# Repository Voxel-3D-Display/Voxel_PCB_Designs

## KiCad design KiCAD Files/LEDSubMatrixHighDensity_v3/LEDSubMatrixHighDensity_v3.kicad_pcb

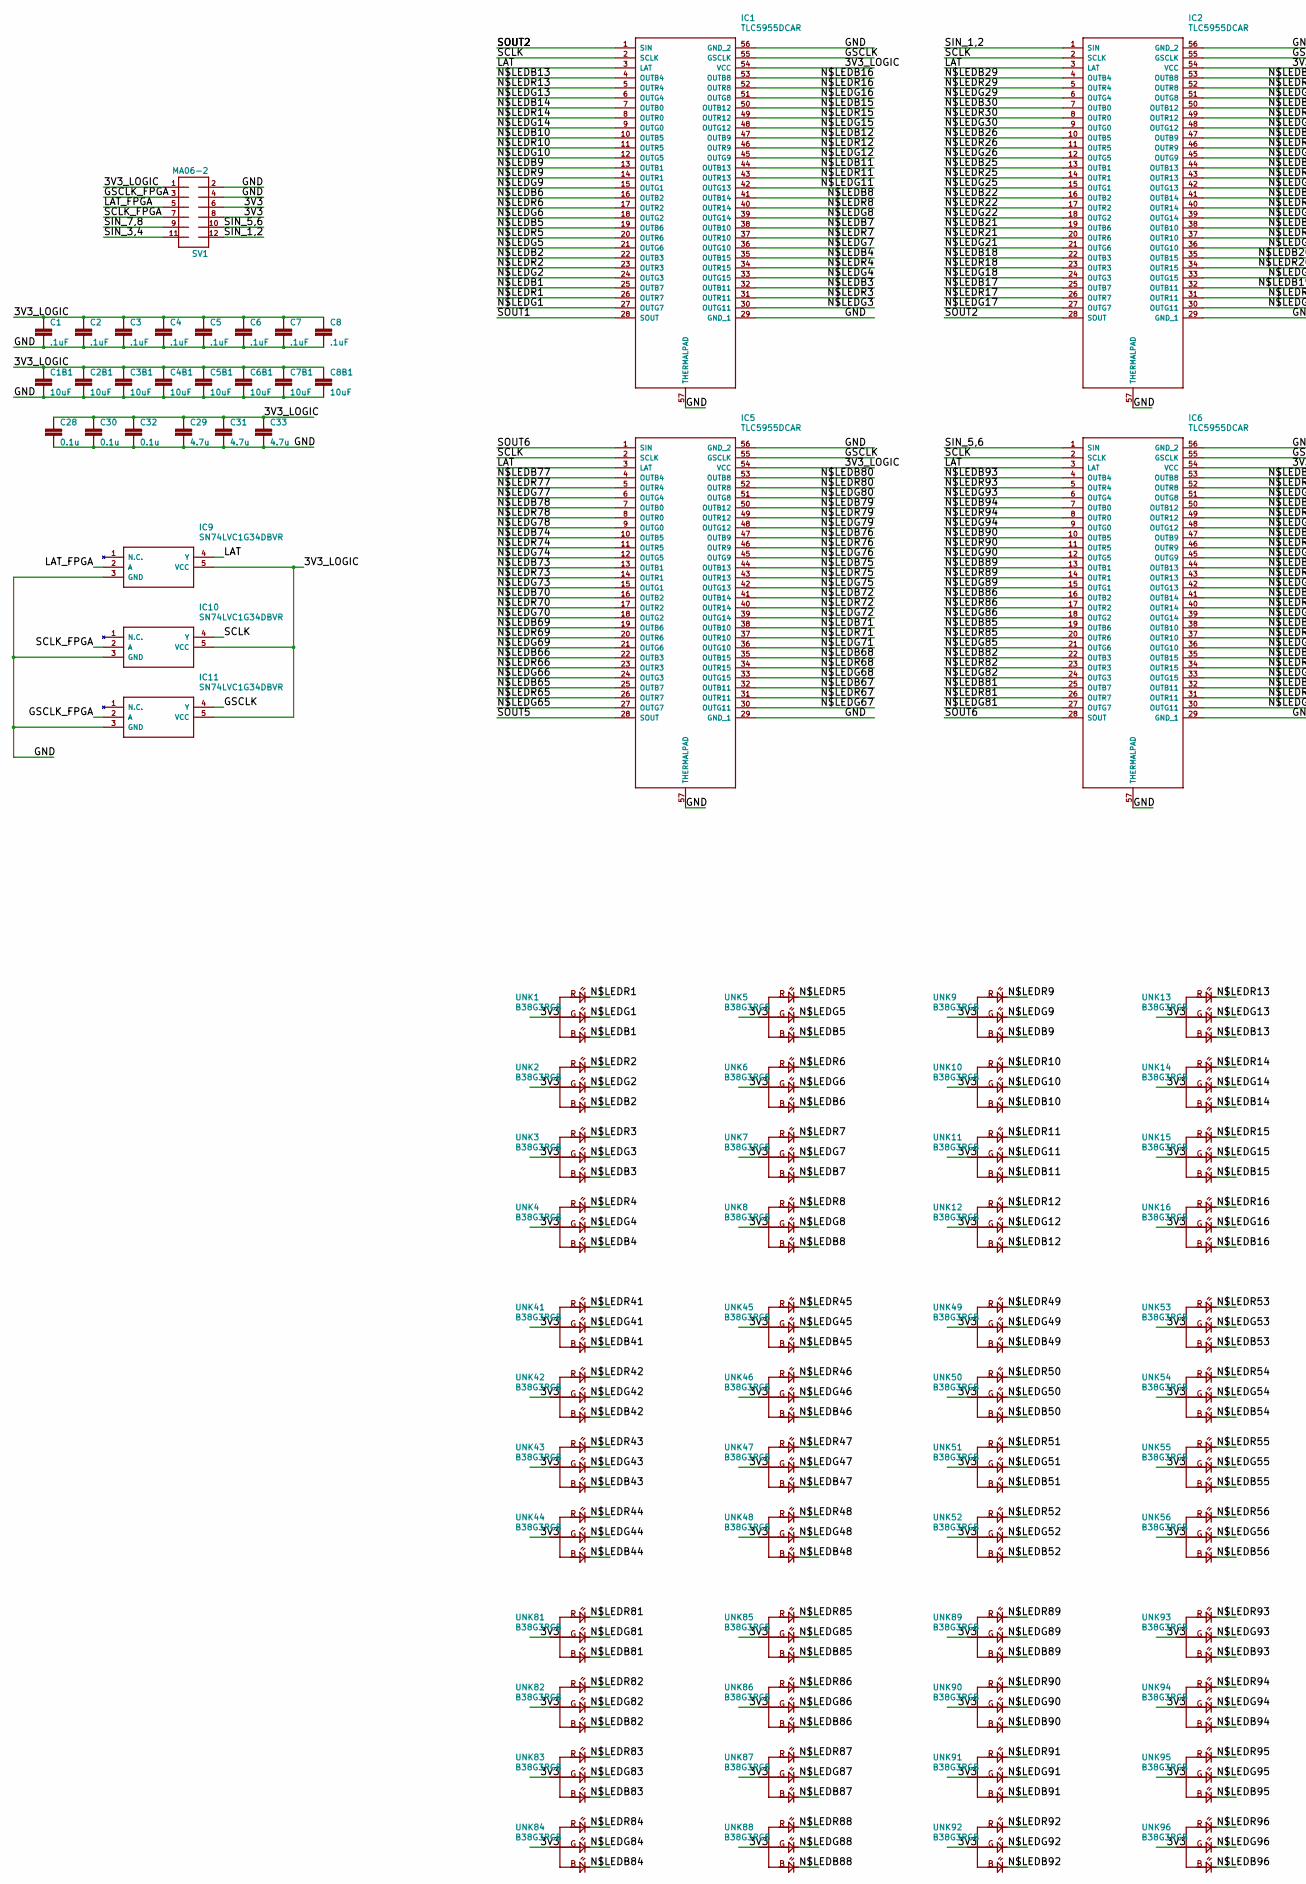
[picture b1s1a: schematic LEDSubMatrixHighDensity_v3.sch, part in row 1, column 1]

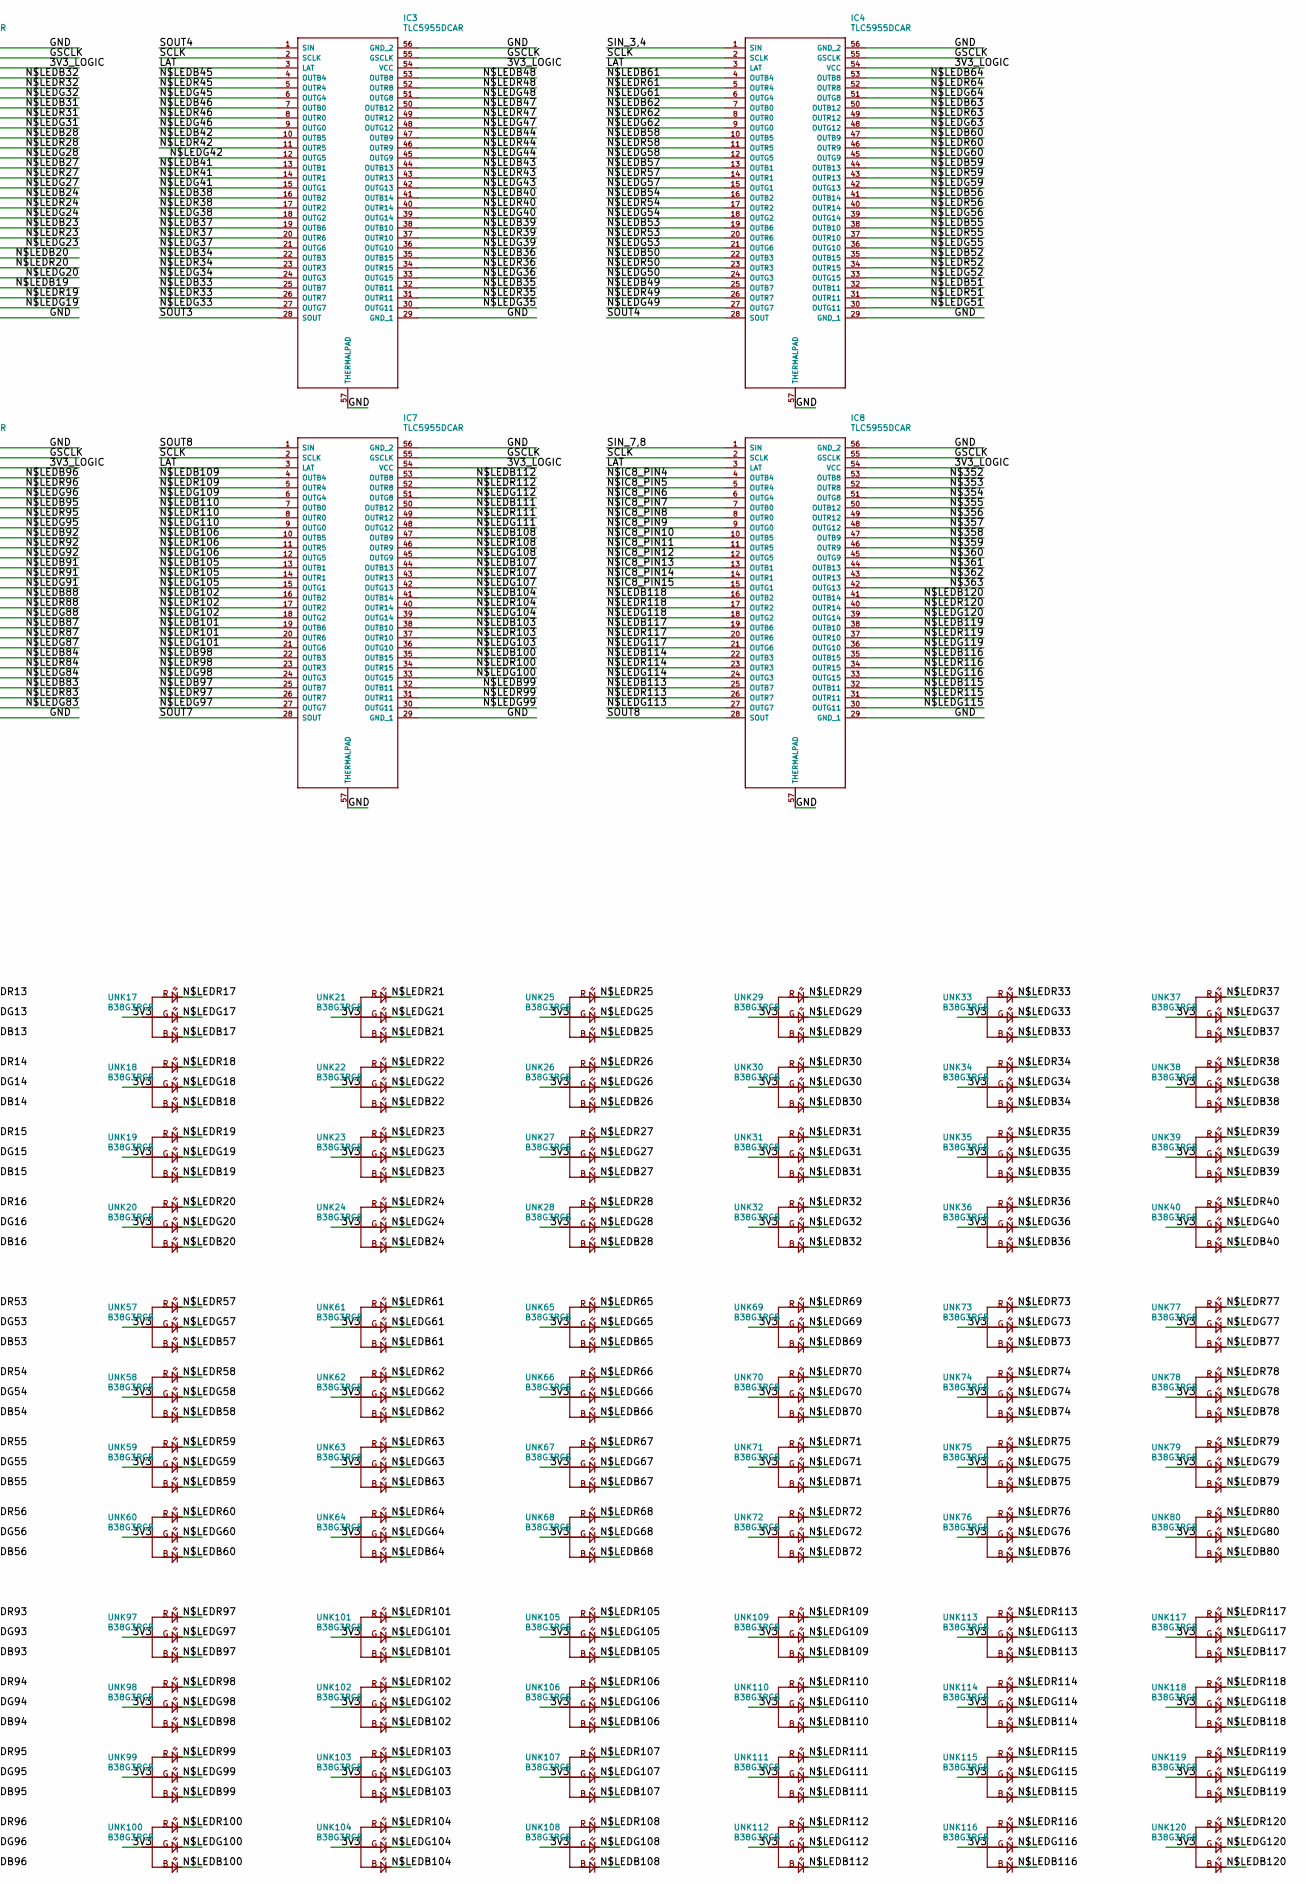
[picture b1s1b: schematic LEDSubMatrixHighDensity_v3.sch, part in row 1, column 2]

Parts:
C1, C2, C3, C4, C5, C6, C7, C8: .1uF; C0402
C1B1, C2B1, C3B1, C4B1, C5B1, C6B1, C7B1, C8B1: 10uF; C0402
C28, C30, C32: 0.1u; C0402
C29, C31, C33: 4.7u; C0402
IC1, IC2, IC3, IC4, IC5, IC6, IC7, IC8: TLC5955DCAR; SOP50P810X120-57N
IC9, IC10, IC11: SN74LVC1G34DBVR; SOT95P280X145-5N
SV1: MA06-2
UNK1, UNK2, UNK3, UNK4, UNK5, UNK6, UNK7, UNK8, UNK9, UNK10, UNK11, UNK12, UNK13, UNK14, UNK15, UNK16, UNK17, UNK18, UNK19, UNK20, UNK21, UNK22, UNK23, UNK24, UNK25, UNK26, UNK27, UNK28, UNK29, UNK30, UNK31, UNK32, UNK33, UNK34, UNK35, UNK36, UNK37, UNK38, UNK39, UNK40, UNK41, UNK42, UNK43, UNK44, UNK45, UNK46, UNK47, UNK48, UNK49, UNK50, UNK51, UNK52, UNK53, UNK54, UNK55, UNK56, UNK57, UNK58, UNK59, UNK60, UNK61, UNK62, UNK63, UNK64, UNK65, UNK66, UNK67, UNK68, UNK69, UNK70, UNK71, UNK72, UNK73, UNK74, UNK75, UNK76, UNK77, UNK78, UNK79, UNK80, UNK81, UNK82, UNK83, UNK84, UNK85, UNK86, UNK87, UNK88, UNK89, UNK90, UNK91, UNK92, UNK93, UNK94, UNK95, UNK96, UNK97, UNK98, UNK99, UNK100, UNK101, UNK102, UNK103, UNK104, UNK105, UNK106, UNK107, UNK108, UNK109, UNK110, UNK111, UNK112, UNK113, UNK114, UNK115, UNK116, UNK117, UNK118, UNK119, UNK120: B38G3RGB

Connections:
/3V3: SV1.6, SV1.8, UNK1.3 (COM), UNK2.3 (COM), UNK3.3 (COM), UNK4.3 (COM), UNK5.3 (COM), UNK6.3 (COM), UNK7.3 (COM), UNK8.3 (COM), UNK9.3 (COM), UNK10.3 (COM), UNK11.3 (COM), UNK12.3 (COM), UNK13.3 (COM), UNK14.3 (COM), UNK15.3 (COM), UNK16.3 (COM), UNK17.3 (COM), UNK18.3 (COM), UNK19.3 (COM), UNK20.3 (COM), UNK21.3 (COM), UNK22.3 (COM), UNK23.3 (COM), UNK24.3 (COM), UNK25.3 (COM), UNK26.3 (COM), UNK27.3 (COM), UNK28.3 (COM), UNK29.3 (COM), UNK30.3 (COM), UNK31.3 (COM), UNK32.3 (COM), UNK33.3 (COM), UNK34.3 (COM), UNK35.3 (COM), UNK36.3 (COM), UNK37.3 (COM), UNK38.3 (COM), UNK39.3 (COM), UNK40.3 (COM), UNK41.3 (COM), UNK42.3 (COM), UNK43.3 (COM), UNK44.3 (COM), UNK45.3 (COM), UNK46.3 (COM), UNK47.3 (COM), UNK48.3 (COM), UNK49.3 (COM), UNK50.3 (COM), UNK51.3 (COM), UNK52.3 (COM), UNK53.3 (COM), UNK54.3 (COM), UNK55.3 (COM), UNK56.3 (COM), UNK57.3 (COM), UNK58.3 (COM), UNK59.3 (COM), UNK60.3 (COM), UNK61.3 (COM), UNK62.3 (COM), UNK63.3 (COM), UNK64.3 (COM), UNK65.3 (COM), UNK66.3 (COM), UNK67.3 (COM), UNK68.3 (COM), UNK69.3 (COM), UNK70.3 (COM), UNK71.3 (COM), UNK72.3 (COM), UNK73.3 (COM), UNK74.3 (COM), UNK75.3 (COM), UNK76.3 (COM), UNK77.3 (COM), UNK78.3 (COM), UNK79.3 (COM), UNK80.3 (COM), UNK81.3 (COM), UNK82.3 (COM), UNK83.3 (COM), UNK84.3 (COM), UNK85.3 (COM), UNK86.3 (COM), UNK87.3 (COM), UNK88.3 (COM), UNK89.3 (COM), UNK90.3 (COM), UNK91.3 (COM), UNK92.3 (COM), UNK93.3 (COM), UNK94.3 (COM), UNK95.3 (COM), UNK96.3 (COM), UNK97.3 (COM), UNK98.3 (COM), UNK99.3 (COM), UNK100.3 (COM), UNK101.3 (COM), UNK102.3 (COM), UNK103.3 (COM), UNK104.3 (COM), UNK105.3 (COM), UNK106.3 (COM), UNK107.3 (COM), UNK108.3 (COM), UNK109.3 (COM), UNK110.3 (COM), UNK111.3 (COM), UNK112.3 (COM), UNK113.3 (COM), UNK114.3 (COM), UNK115.3 (COM), UNK116.3 (COM), UNK117.3 (COM), UNK118.3 (COM), UNK119.3 (COM), UNK120.3 (COM)
/3V3_LOGIC: C1.1, C1B1.1, C2.1, C2B1.1, C3.1, C3B1.1, C4.1, C4B1.1, C5.1, C5B1.1, C6.1, C6B1.1, C7.1, C7B1.1, C8.1, C8B1.1, C28.1, C29.1, C30.1, C31.1, C32.1, C33.1, IC1.54 (VCC), IC2.54 (VCC), IC3.54 (VCC), IC4.54 (VCC), IC5.54 (VCC), IC6.54 (VCC), IC7.54 (VCC), IC8.54 (VCC), IC9.5 (VCC), IC10.5 (VCC), IC11.5 (VCC), SV1.1
/GND: C1.2, C1B1.2, C2.2, C2B1.2, C3.2, C3B1.2, C4.2, C4B1.2, C5.2, C5B1.2, C6.2, C6B1.2, C7.2, C7B1.2, C8.2, C8B1.2, C28.2, C29.2, C30.2, C31.2, C32.2, C33.2, IC1.56 (GND_2), IC2.56 (GND_2), IC3.56 (GND_2), IC4.56 (GND_2), IC5.29 (GND_1), IC5.56 (GND_2), IC5.57 (THERMALPAD), IC6.29 (GND_1), IC6.56 (GND_2), IC6.57 (THERMALPAD), IC7.29 (GND_1), IC7.56 (GND_2), IC7.57 (THERMALPAD), IC8.29 (GND_1), IC8.56 (GND_2), IC8.57 (THERMALPAD), IC9.3 (GND), IC10.3 (GND), IC11.3 (GND), SV1.2, SV1.4
/GSCLK: IC1.55 (GSCLK), IC2.55 (GSCLK), IC3.55 (GSCLK), IC4.55 (GSCLK), IC5.55 (GSCLK), IC6.55 (GSCLK), IC7.55 (GSCLK), IC8.55 (GSCLK), IC11.4 (Y)
/GSCLK_FPGA: IC11.2 (A), SV1.3
/LAT: IC1.3 (LAT), IC2.3 (LAT), IC3.3 (LAT), IC4.3 (LAT), IC5.3 (LAT), IC6.3 (LAT), IC7.3 (LAT), IC8.3 (LAT), IC9.4 (Y)
/LAT_FPGA: IC9.2 (A), SV1.5
/N$352: IC8.53 (OUTB8)
/N$353: IC8.52 (OUTR8)
/N$354: IC8.51 (OUTG8)
/N$355: IC8.50 (OUTB12)
/N$356: IC8.49 (OUTR12)
/N$357: IC8.48 (OUTG12)
/N$358: IC8.47 (OUTB9)
/N$359: IC8.46 (OUTR9)
/N$360: IC8.45 (OUTG9)
/N$361: IC8.44 (OUTB13)
/N$362: IC8.43 (OUTR13)
/N$363: IC8.42 (OUTG13)
/N$IC8_PIN4: IC8.4 (OUTB4)
/N$IC8_PIN5: IC8.5 (OUTR4)
/N$IC8_PIN6: IC8.6 (OUTG4)
/N$IC8_PIN7: IC8.7 (OUTB0)
/N$IC8_PIN8: IC8.8 (OUTR0)
/N$IC8_PIN9: IC8.9 (OUTG0)
/N$IC8_PIN10: IC8.10 (OUTB5)
/N$IC8_PIN11: IC8.11 (OUTR5)
/N$IC8_PIN12: IC8.12 (OUTG5)
/N$IC8_PIN13: IC8.13 (OUTB1)
/N$IC8_PIN14: IC8.14 (OUTR1)
/N$IC8_PIN15: IC8.15 (OUTG1)
/N$LEDB1: UNK1.2 (BLUE)
/N$LEDB2: IC1.22 (OUTB3), UNK2.2 (BLUE)
/N$LEDB3: UNK3.2 (BLUE)
/N$LEDB4: IC1.35 (OUTB15), UNK4.2 (BLUE)
/N$LEDB5: IC1.19 (OUTB6), UNK5.2 (BLUE)
/N$LEDB6: IC1.16 (OUTB2), UNK6.2 (BLUE)
/N$LEDB7: IC1.38 (OUTB10), UNK7.2 (BLUE)
/N$LEDB8: IC1.41 (OUTB14), UNK8.2 (BLUE)
/N$LEDB9: IC1.13 (OUTB1), UNK9.2 (BLUE)
/N$LEDB10: IC1.10 (OUTB5), UNK10.2 (BLUE)
/N$LEDB11: IC1.44 (OUTB13), UNK11.2 (BLUE)
/N$LEDB12: IC1.47 (OUTB9), UNK12.2 (BLUE)
/N$LEDB13: IC1.4 (OUTB4), UNK13.2 (BLUE)
/N$LEDB14: IC1.7 (OUTB0), UNK14.2 (BLUE)
/N$LEDB15: IC1.50 (OUTB12), UNK15.2 (BLUE)
/N$LEDB16: IC1.53 (OUTB8), UNK16.2 (BLUE)
/N$LEDB17: UNK17.2 (BLUE)
/N$LEDB18: IC2.22 (OUTB3), UNK18.2 (BLUE)
/N$LEDB19: UNK19.2 (BLUE)
/N$LEDB20: IC2.35 (OUTB15), UNK20.2 (BLUE)
/N$LEDB21: IC2.19 (OUTB6), UNK21.2 (BLUE)
/N$LEDB22: IC2.16 (OUTB2), UNK22.2 (BLUE)
/N$LEDB23: IC2.38 (OUTB10), UNK23.2 (BLUE)
/N$LEDB24: IC2.41 (OUTB14), UNK24.2 (BLUE)
/N$LEDB25: IC2.13 (OUTB1), UNK25.2 (BLUE)
/N$LEDB26: IC2.10 (OUTB5), UNK26.2 (BLUE)
/N$LEDB27: IC2.44 (OUTB13), UNK27.2 (BLUE)
/N$LEDB28: IC2.47 (OUTB9), UNK28.2 (BLUE)
/N$LEDB29: IC2.4 (OUTB4), UNK29.2 (BLUE)
/N$LEDB30: IC2.7 (OUTB0), UNK30.2 (BLUE)
/N$LEDB31: IC2.50 (OUTB12), UNK31.2 (BLUE)
/N$LEDB32: IC2.53 (OUTB8), UNK32.2 (BLUE)
/N$LEDB33: UNK33.2 (BLUE)
/N$LEDB34: IC3.22 (OUTB3), UNK34.2 (BLUE)
/N$LEDB35: UNK35.2 (BLUE)
/N$LEDB36: IC3.35 (OUTB15), UNK36.2 (BLUE)
/N$LEDB37: IC3.19 (OUTB6), UNK37.2 (BLUE)
/N$LEDB38: IC3.16 (OUTB2), UNK38.2 (BLUE)
/N$LEDB39: IC3.38 (OUTB10), UNK39.2 (BLUE)
/N$LEDB40: IC3.41 (OUTB14), UNK40.2 (BLUE)
/N$LEDB41: IC3.13 (OUTB1), UNK41.2 (BLUE)
/N$LEDB42: IC3.10 (OUTB5), UNK42.2 (BLUE)
/N$LEDB43: IC3.44 (OUTB13), UNK43.2 (BLUE)
/N$LEDB44: IC3.47 (OUTB9), UNK44.2 (BLUE)
/N$LEDB45: IC3.4 (OUTB4), UNK45.2 (BLUE)
/N$LEDB46: IC3.7 (OUTB0), UNK46.2 (BLUE)
/N$LEDB47: IC3.50 (OUTB12), UNK47.2 (BLUE)
/N$LEDB48: IC3.53 (OUTB8), UNK48.2 (BLUE)
/N$LEDB49: UNK49.2 (BLUE)
/N$LEDB50: IC4.22 (OUTB3), UNK50.2 (BLUE)
/N$LEDB51: UNK51.2 (BLUE)
/N$LEDB52: IC4.35 (OUTB15), UNK52.2 (BLUE)
/N$LEDB53: IC4.19 (OUTB6), UNK53.2 (BLUE)
/N$LEDB54: IC4.16 (OUTB2), UNK54.2 (BLUE)
/N$LEDB55: IC4.38 (OUTB10), UNK55.2 (BLUE)
/N$LEDB56: IC4.41 (OUTB14), UNK56.2 (BLUE)
/N$LEDB57: IC4.13 (OUTB1), UNK57.2 (BLUE)
/N$LEDB58: IC4.10 (OUTB5), UNK58.2 (BLUE)
/N$LEDB59: IC4.44 (OUTB13), UNK59.2 (BLUE)
/N$LEDB60: IC4.47 (OUTB9), UNK60.2 (BLUE)
/N$LEDB61: IC4.4 (OUTB4), UNK61.2 (BLUE)
/N$LEDB62: IC4.7 (OUTB0), UNK62.2 (BLUE)
/N$LEDB63: IC4.50 (OUTB12), UNK63.2 (BLUE)
/N$LEDB64: IC4.53 (OUTB8), UNK64.2 (BLUE)
/N$LEDB65: IC5.25 (OUTB7), UNK65.2 (BLUE)
/N$LEDB66: IC5.22 (OUTB3), UNK66.2 (BLUE)
/N$LEDB67: IC5.32 (OUTB11), UNK67.2 (BLUE)
/N$LEDB68: IC5.35 (OUTB15), UNK68.2 (BLUE)
/N$LEDB69: IC5.19 (OUTB6), UNK69.2 (BLUE)
/N$LEDB70: IC5.16 (OUTB2), UNK70.2 (BLUE)
/N$LEDB71: IC5.38 (OUTB10), UNK71.2 (BLUE)
/N$LEDB72: IC5.41 (OUTB14), UNK72.2 (BLUE)
/N$LEDB73: IC5.13 (OUTB1), UNK73.2 (BLUE)
/N$LEDB74: IC5.10 (OUTB5), UNK74.2 (BLUE)
/N$LEDB75: IC5.44 (OUTB13), UNK75.2 (BLUE)
/N$LEDB76: IC5.47 (OUTB9), UNK76.2 (BLUE)
/N$LEDB77: IC5.4 (OUTB4), UNK77.2 (BLUE)
/N$LEDB78: IC5.7 (OUTB0), UNK78.2 (BLUE)
/N$LEDB79: IC5.50 (OUTB12), UNK79.2 (BLUE)
/N$LEDB80: IC5.53 (OUTB8), UNK80.2 (BLUE)
/N$LEDB81: IC6.25 (OUTB7), UNK81.2 (BLUE)
/N$LEDB82: IC6.22 (OUTB3), UNK82.2 (BLUE)
/N$LEDB83: IC6.32 (OUTB11), UNK83.2 (BLUE)
/N$LEDB84: IC6.35 (OUTB15), UNK84.2 (BLUE)
/N$LEDB85: IC6.19 (OUTB6), UNK85.2 (BLUE)
/N$LEDB86: IC6.16 (OUTB2), UNK86.2 (BLUE)
/N$LEDB87: IC6.38 (OUTB10), UNK87.2 (BLUE)
/N$LEDB88: IC6.41 (OUTB14), UNK88.2 (BLUE)
/N$LEDB89: IC6.13 (OUTB1), UNK89.2 (BLUE)
/N$LEDB90: IC6.10 (OUTB5), UNK90.2 (BLUE)
/N$LEDB91: IC6.44 (OUTB13), UNK91.2 (BLUE)
/N$LEDB92: IC6.47 (OUTB9), UNK92.2 (BLUE)
/N$LEDB93: IC6.4 (OUTB4), UNK93.2 (BLUE)
/N$LEDB94: IC6.7 (OUTB0), UNK94.2 (BLUE)
/N$LEDB95: IC6.50 (OUTB12), UNK95.2 (BLUE)
/N$LEDB96: IC6.53 (OUTB8), UNK96.2 (BLUE)
/N$LEDB97: IC7.25 (OUTB7), UNK97.2 (BLUE)
/N$LEDB98: IC7.22 (OUTB3), UNK98.2 (BLUE)
/N$LEDB99: IC7.32 (OUTB11), UNK99.2 (BLUE)
/N$LEDB100: IC7.35 (OUTB15), UNK100.2 (BLUE)
/N$LEDB101: IC7.19 (OUTB6), UNK101.2 (BLUE)
/N$LEDB102: IC7.16 (OUTB2), UNK102.2 (BLUE)
/N$LEDB103: IC7.38 (OUTB10), UNK103.2 (BLUE)
/N$LEDB104: IC7.41 (OUTB14), UNK104.2 (BLUE)
/N$LEDB105: IC7.13 (OUTB1), UNK105.2 (BLUE)
/N$LEDB106: IC7.10 (OUTB5), UNK106.2 (BLUE)
/N$LEDB107: IC7.44 (OUTB13), UNK107.2 (BLUE)
/N$LEDB108: IC7.47 (OUTB9), UNK108.2 (BLUE)
/N$LEDB109: IC7.4 (OUTB4), UNK109.2 (BLUE)
/N$LEDB110: IC7.7 (OUTB0), UNK110.2 (BLUE)
/N$LEDB111: IC7.50 (OUTB12), UNK111.2 (BLUE)
/N$LEDB112: IC7.53 (OUTB8), UNK112.2 (BLUE)
/N$LEDB113: IC8.25 (OUTB7), UNK113.2 (BLUE)
/N$LEDB114: IC8.22 (OUTB3), UNK114.2 (BLUE)
/N$LEDB115: IC8.32 (OUTB11), UNK115.2 (BLUE)
/N$LEDB116: IC8.35 (OUTB15), UNK116.2 (BLUE)
/N$LEDB117: IC8.19 (OUTB6), UNK117.2 (BLUE)
/N$LEDB118: IC8.16 (OUTB2), UNK118.2 (BLUE)
/N$LEDB119: IC8.38 (OUTB10), UNK119.2 (BLUE)
/N$LEDB120: IC8.41 (OUTB14), UNK120.2 (BLUE)
/N$LEDG1: UNK1.1 (GREEN)
/N$LEDG2: UNK2.1 (GREEN)
/N$LEDG3: UNK3.1 (GREEN)
/N$LEDG4: UNK4.1 (GREEN)
/N$LEDG5: IC1.21 (OUTG6), UNK5.1 (GREEN)
/N$LEDG6: IC1.18 (OUTG2), UNK6.1 (GREEN)
/N$LEDG7: IC1.36 (OUTG10), UNK7.1 (GREEN)
/N$LEDG8: IC1.39 (OUTG14), UNK8.1 (GREEN)
/N$LEDG9: IC1.15 (OUTG1), UNK9.1 (GREEN)
/N$LEDG10: IC1.12 (OUTG5), UNK10.1 (GREEN)
/N$LEDG11: IC1.42 (OUTG13), UNK11.1 (GREEN)
/N$LEDG12: IC1.45 (OUTG9), UNK12.1 (GREEN)
/N$LEDG13: IC1.6 (OUTG4), UNK13.1 (GREEN)
/N$LEDG14: IC1.9 (OUTG0), UNK14.1 (GREEN)
/N$LEDG15: IC1.48 (OUTG12), UNK15.1 (GREEN)
/N$LEDG16: IC1.51 (OUTG8), UNK16.1 (GREEN)
/N$LEDG17: UNK17.1 (GREEN)
/N$LEDG18: UNK18.1 (GREEN)
/N$LEDG19: UNK19.1 (GREEN)
/N$LEDG20: UNK20.1 (GREEN)
/N$LEDG21: IC2.21 (OUTG6), UNK21.1 (GREEN)
/N$LEDG22: IC2.18 (OUTG2), UNK22.1 (GREEN)
/N$LEDG23: IC2.36 (OUTG10), UNK23.1 (GREEN)
/N$LEDG24: IC2.39 (OUTG14), UNK24.1 (GREEN)
/N$LEDG25: IC2.15 (OUTG1), UNK25.1 (GREEN)
/N$LEDG26: IC2.12 (OUTG5), UNK26.1 (GREEN)
/N$LEDG27: IC2.42 (OUTG13), UNK27.1 (GREEN)
/N$LEDG28: IC2.45 (OUTG9), UNK28.1 (GREEN)
/N$LEDG29: IC2.6 (OUTG4), UNK29.1 (GREEN)
/N$LEDG30: IC2.9 (OUTG0), UNK30.1 (GREEN)
/N$LEDG31: IC2.48 (OUTG12), UNK31.1 (GREEN)
/N$LEDG32: IC2.51 (OUTG8), UNK32.1 (GREEN)
/N$LEDG33: UNK33.1 (GREEN)
/N$LEDG34: UNK34.1 (GREEN)
/N$LEDG35: UNK35.1 (GREEN)
/N$LEDG36: UNK36.1 (GREEN)
/N$LEDG37: IC3.21 (OUTG6), UNK37.1 (GREEN)
/N$LEDG38: IC3.18 (OUTG2), UNK38.1 (GREEN)
/N$LEDG39: IC3.36 (OUTG10), UNK39.1 (GREEN)
/N$LEDG40: IC3.39 (OUTG14), UNK40.1 (GREEN)
/N$LEDG41: IC3.15 (OUTG1), UNK41.1 (GREEN)
/N$LEDG42: IC3.12 (OUTG5), UNK42.1 (GREEN)
/N$LEDG43: IC3.42 (OUTG13), UNK43.1 (GREEN)
/N$LEDG44: IC3.45 (OUTG9), UNK44.1 (GREEN)
/N$LEDG45: IC3.6 (OUTG4), UNK45.1 (GREEN)
/N$LEDG46: IC3.9 (OUTG0), UNK46.1 (GREEN)
/N$LEDG47: IC3.48 (OUTG12), UNK47.1 (GREEN)
/N$LEDG48: IC3.51 (OUTG8), UNK48.1 (GREEN)
/N$LEDG49: UNK49.1 (GREEN)
/N$LEDG50: UNK50.1 (GREEN)
/N$LEDG51: UNK51.1 (GREEN)
/N$LEDG52: UNK52.1 (GREEN)
/N$LEDG53: IC4.21 (OUTG6), UNK53.1 (GREEN)
/N$LEDG54: IC4.18 (OUTG2), UNK54.1 (GREEN)
/N$LEDG55: IC4.36 (OUTG10), UNK55.1 (GREEN)
/N$LEDG56: IC4.39 (OUTG14), UNK56.1 (GREEN)
/N$LEDG57: IC4.15 (OUTG1), UNK57.1 (GREEN)
/N$LEDG58: IC4.12 (OUTG5), UNK58.1 (GREEN)
/N$LEDG59: IC4.42 (OUTG13), UNK59.1 (GREEN)
/N$LEDG60: IC4.45 (OUTG9), UNK60.1 (GREEN)
/N$LEDG61: IC4.6 (OUTG4), UNK61.1 (GREEN)
/N$LEDG62: IC4.9 (OUTG0), UNK62.1 (GREEN)
/N$LEDG63: IC4.48 (OUTG12), UNK63.1 (GREEN)
/N$LEDG64: IC4.51 (OUTG8), UNK64.1 (GREEN)
/N$LEDG65: IC5.27 (OUTG7), UNK65.1 (GREEN)
/N$LEDG66: IC5.24 (OUTG3), UNK66.1 (GREEN)
/N$LEDG67: IC5.30 (OUTG11), UNK67.1 (GREEN)
/N$LEDG68: IC5.33 (OUTG15), UNK68.1 (GREEN)
/N$LEDG69: IC5.21 (OUTG6), UNK69.1 (GREEN)
/N$LEDG70: IC5.18 (OUTG2), UNK70.1 (GREEN)
/N$LEDG71: IC5.36 (OUTG10), UNK71.1 (GREEN)
/N$LEDG72: IC5.39 (OUTG14), UNK72.1 (GREEN)
/N$LEDG73: IC5.15 (OUTG1), UNK73.1 (GREEN)
/N$LEDG74: IC5.12 (OUTG5), UNK74.1 (GREEN)
/N$LEDG75: IC5.42 (OUTG13), UNK75.1 (GREEN)
/N$LEDG76: IC5.45 (OUTG9), UNK76.1 (GREEN)
/N$LEDG77: IC5.6 (OUTG4), UNK77.1 (GREEN)
/N$LEDG78: IC5.9 (OUTG0), UNK78.1 (GREEN)
/N$LEDG79: IC5.48 (OUTG12), UNK79.1 (GREEN)
/N$LEDG80: IC5.51 (OUTG8), UNK80.1 (GREEN)
/N$LEDG81: IC6.27 (OUTG7), UNK81.1 (GREEN)
/N$LEDG82: IC6.24 (OUTG3), UNK82.1 (GREEN)
/N$LEDG83: IC6.30 (OUTG11), UNK83.1 (GREEN)
/N$LEDG84: IC6.33 (OUTG15), UNK84.1 (GREEN)
/N$LEDG85: IC6.21 (OUTG6), UNK85.1 (GREEN)
/N$LEDG86: IC6.18 (OUTG2), UNK86.1 (GREEN)
/N$LEDG87: IC6.36 (OUTG10), UNK87.1 (GREEN)
/N$LEDG88: IC6.39 (OUTG14), UNK88.1 (GREEN)
/N$LEDG89: IC6.15 (OUTG1), UNK89.1 (GREEN)
/N$LEDG90: IC6.12 (OUTG5), UNK90.1 (GREEN)
/N$LEDG91: IC6.42 (OUTG13), UNK91.1 (GREEN)
/N$LEDG92: IC6.45 (OUTG9), UNK92.1 (GREEN)
/N$LEDG93: IC6.6 (OUTG4), UNK93.1 (GREEN)
/N$LEDG94: IC6.9 (OUTG0), UNK94.1 (GREEN)
/N$LEDG95: IC6.48 (OUTG12), UNK95.1 (GREEN)
/N$LEDG96: IC6.51 (OUTG8), UNK96.1 (GREEN)
/N$LEDG97: IC7.27 (OUTG7), UNK97.1 (GREEN)
/N$LEDG98: IC7.24 (OUTG3), UNK98.1 (GREEN)
/N$LEDG99: IC7.30 (OUTG11), UNK99.1 (GREEN)
/N$LEDG100: IC7.33 (OUTG15), UNK100.1 (GREEN)
/N$LEDG101: IC7.21 (OUTG6), UNK101.1 (GREEN)
/N$LEDG102: IC7.18 (OUTG2), UNK102.1 (GREEN)
/N$LEDG103: IC7.36 (OUTG10), UNK103.1 (GREEN)
/N$LEDG104: IC7.39 (OUTG14), UNK104.1 (GREEN)
/N$LEDG105: IC7.15 (OUTG1), UNK105.1 (GREEN)
/N$LEDG106: IC7.12 (OUTG5), UNK106.1 (GREEN)
/N$LEDG107: IC7.42 (OUTG13), UNK107.1 (GREEN)
/N$LEDG108: IC7.45 (OUTG9), UNK108.1 (GREEN)
/N$LEDG109: IC7.6 (OUTG4), UNK109.1 (GREEN)
/N$LEDG110: IC7.9 (OUTG0), UNK110.1 (GREEN)
/N$LEDG111: IC7.48 (OUTG12), UNK111.1 (GREEN)
/N$LEDG112: IC7.51 (OUTG8), UNK112.1 (GREEN)
/N$LEDG113: IC8.27 (OUTG7), UNK113.1 (GREEN)
/N$LEDG114: IC8.24 (OUTG3), UNK114.1 (GREEN)
/N$LEDG115: IC8.30 (OUTG11), UNK115.1 (GREEN)
/N$LEDG116: IC8.33 (OUTG15), UNK116.1 (GREEN)
/N$LEDG117: IC8.21 (OUTG6), UNK117.1 (GREEN)
/N$LEDG118: IC8.18 (OUTG2), UNK118.1 (GREEN)
/N$LEDG119: IC8.36 (OUTG10), UNK119.1 (GREEN)
/N$LEDG120: IC8.39 (OUTG14), UNK120.1 (GREEN)
/N$LEDR1: UNK1.4 (RED)
/N$LEDR2: UNK2.4 (RED)
/N$LEDR3: UNK3.4 (RED)
/N$LEDR4: UNK4.4 (RED)
/N$LEDR5: IC1.20 (OUTR6), UNK5.4 (RED)
/N$LEDR6: IC1.17 (OUTR2), UNK6.4 (RED)
/N$LEDR7: IC1.37 (OUTR10), UNK7.4 (RED)
/N$LEDR8: IC1.40 (OUTR14), UNK8.4 (RED)
/N$LEDR9: IC1.14 (OUTR1), UNK9.4 (RED)
/N$LEDR10: IC1.11 (OUTR5), UNK10.4 (RED)
/N$LEDR11: IC1.43 (OUTR13), UNK11.4 (RED)
/N$LEDR12: IC1.46 (OUTR9), UNK12.4 (RED)
/N$LEDR13: IC1.5 (OUTR4), UNK13.4 (RED)
/N$LEDR14: IC1.8 (OUTR0), UNK14.4 (RED)
/N$LEDR15: IC1.49 (OUTR12), UNK15.4 (RED)
/N$LEDR16: IC1.52 (OUTR8), UNK16.4 (RED)
/N$LEDR17: UNK17.4 (RED)
/N$LEDR18: UNK18.4 (RED)
/N$LEDR19: UNK19.4 (RED)
/N$LEDR20: UNK20.4 (RED)
/N$LEDR21: IC2.20 (OUTR6), UNK21.4 (RED)
/N$LEDR22: IC2.17 (OUTR2), UNK22.4 (RED)
/N$LEDR23: IC2.37 (OUTR10), UNK23.4 (RED)
/N$LEDR24: IC2.40 (OUTR14), UNK24.4 (RED)
/N$LEDR25: IC2.14 (OUTR1), UNK25.4 (RED)
/N$LEDR26: IC2.11 (OUTR5), UNK26.4 (RED)
/N$LEDR27: IC2.43 (OUTR13), UNK27.4 (RED)
/N$LEDR28: IC2.46 (OUTR9), UNK28.4 (RED)
/N$LEDR29: IC2.5 (OUTR4), UNK29.4 (RED)
/N$LEDR30: IC2.8 (OUTR0), UNK30.4 (RED)
/N$LEDR31: IC2.49 (OUTR12), UNK31.4 (RED)
/N$LEDR32: IC2.52 (OUTR8), UNK32.4 (RED)
/N$LEDR33: UNK33.4 (RED)
/N$LEDR34: UNK34.4 (RED)
/N$LEDR35: UNK35.4 (RED)
/N$LEDR36: UNK36.4 (RED)
/N$LEDR37: IC3.20 (OUTR6), UNK37.4 (RED)
/N$LEDR38: IC3.17 (OUTR2), UNK38.4 (RED)
/N$LEDR39: IC3.37 (OUTR10), UNK39.4 (RED)
/N$LEDR40: IC3.40 (OUTR14), UNK40.4 (RED)
/N$LEDR41: IC3.14 (OUTR1), UNK41.4 (RED)
/N$LEDR42: IC3.11 (OUTR5), UNK42.4 (RED)
/N$LEDR43: IC3.43 (OUTR13), UNK43.4 (RED)
/N$LEDR44: IC3.46 (OUTR9), UNK44.4 (RED)
/N$LEDR45: IC3.5 (OUTR4), UNK45.4 (RED)
/N$LEDR46: IC3.8 (OUTR0), UNK46.4 (RED)
/N$LEDR47: IC3.49 (OUTR12), UNK47.4 (RED)
/N$LEDR48: IC3.52 (OUTR8), UNK48.4 (RED)
/N$LEDR49: UNK49.4 (RED)
/N$LEDR50: UNK50.4 (RED)
/N$LEDR51: UNK51.4 (RED)
/N$LEDR52: UNK52.4 (RED)
/N$LEDR53: IC4.20 (OUTR6), UNK53.4 (RED)
/N$LEDR54: IC4.17 (OUTR2), UNK54.4 (RED)
/N$LEDR55: IC4.37 (OUTR10), UNK55.4 (RED)
/N$LEDR56: IC4.40 (OUTR14), UNK56.4 (RED)
/N$LEDR57: IC4.14 (OUTR1), UNK57.4 (RED)
/N$LEDR58: IC4.11 (OUTR5), UNK58.4 (RED)
/N$LEDR59: IC4.43 (OUTR13), UNK59.4 (RED)
/N$LEDR60: IC4.46 (OUTR9), UNK60.4 (RED)
/N$LEDR61: IC4.5 (OUTR4), UNK61.4 (RED)
/N$LEDR62: IC4.8 (OUTR0), UNK62.4 (RED)
/N$LEDR63: IC4.49 (OUTR12), UNK63.4 (RED)
/N$LEDR64: IC4.52 (OUTR8), UNK64.4 (RED)
/N$LEDR65: IC5.26 (OUTR7), UNK65.4 (RED)
/N$LEDR66: IC5.23 (OUTR3), UNK66.4 (RED)
/N$LEDR67: IC5.31 (OUTR11), UNK67.4 (RED)
/N$LEDR68: IC5.34 (OUTR15), UNK68.4 (RED)
/N$LEDR69: IC5.20 (OUTR6), UNK69.4 (RED)
/N$LEDR70: IC5.17 (OUTR2), UNK70.4 (RED)
/N$LEDR71: IC5.37 (OUTR10), UNK71.4 (RED)
/N$LEDR72: IC5.40 (OUTR14), UNK72.4 (RED)
/N$LEDR73: IC5.14 (OUTR1), UNK73.4 (RED)
/N$LEDR74: IC5.11 (OUTR5), UNK74.4 (RED)
/N$LEDR75: IC5.43 (OUTR13), UNK75.4 (RED)
/N$LEDR76: IC5.46 (OUTR9), UNK76.4 (RED)
/N$LEDR77: IC5.5 (OUTR4), UNK77.4 (RED)
/N$LEDR78: IC5.8 (OUTR0), UNK78.4 (RED)
/N$LEDR79: IC5.49 (OUTR12), UNK79.4 (RED)
/N$LEDR80: IC5.52 (OUTR8), UNK80.4 (RED)
/N$LEDR81: IC6.26 (OUTR7), UNK81.4 (RED)
/N$LEDR82: IC6.23 (OUTR3), UNK82.4 (RED)
/N$LEDR83: IC6.31 (OUTR11), UNK83.4 (RED)
/N$LEDR84: IC6.34 (OUTR15), UNK84.4 (RED)
/N$LEDR85: IC6.20 (OUTR6), UNK85.4 (RED)
/N$LEDR86: IC6.17 (OUTR2), UNK86.4 (RED)
/N$LEDR87: IC6.37 (OUTR10), UNK87.4 (RED)
/N$LEDR88: IC6.40 (OUTR14), UNK88.4 (RED)
/N$LEDR89: IC6.14 (OUTR1), UNK89.4 (RED)
/N$LEDR90: IC6.11 (OUTR5), UNK90.4 (RED)
/N$LEDR91: IC6.43 (OUTR13), UNK91.4 (RED)
/N$LEDR92: IC6.46 (OUTR9), UNK92.4 (RED)
/N$LEDR93: IC6.5 (OUTR4), UNK93.4 (RED)
/N$LEDR94: IC6.8 (OUTR0), UNK94.4 (RED)
/N$LEDR95: IC6.49 (OUTR12), UNK95.4 (RED)
/N$LEDR96: IC6.52 (OUTR8), UNK96.4 (RED)
/N$LEDR97: IC7.26 (OUTR7), UNK97.4 (RED)
/N$LEDR98: IC7.23 (OUTR3), UNK98.4 (RED)
/N$LEDR99: IC7.31 (OUTR11), UNK99.4 (RED)
/N$LEDR100: IC7.34 (OUTR15), UNK100.4 (RED)
/N$LEDR101: IC7.20 (OUTR6), UNK101.4 (RED)
/N$LEDR102: IC7.17 (OUTR2), UNK102.4 (RED)
/N$LEDR103: IC7.37 (OUTR10), UNK103.4 (RED)
/N$LEDR104: IC7.40 (OUTR14), UNK104.4 (RED)
/N$LEDR105: IC7.14 (OUTR1), UNK105.4 (RED)
/N$LEDR106: IC7.11 (OUTR5), UNK106.4 (RED)
/N$LEDR107: IC7.43 (OUTR13), UNK107.4 (RED)
/N$LEDR108: IC7.46 (OUTR9), UNK108.4 (RED)
/N$LEDR109: IC7.5 (OUTR4), UNK109.4 (RED)
/N$LEDR110: IC7.8 (OUTR0), UNK110.4 (RED)
/N$LEDR111: IC7.49 (OUTR12), UNK111.4 (RED)
/N$LEDR112: IC7.52 (OUTR8), UNK112.4 (RED)
/N$LEDR113: IC8.26 (OUTR7), UNK113.4 (RED)
/N$LEDR114: IC8.23 (OUTR3), UNK114.4 (RED)
/N$LEDR115: IC8.31 (OUTR11), UNK115.4 (RED)
/N$LEDR116: IC8.34 (OUTR15), UNK116.4 (RED)
/N$LEDR117: IC8.20 (OUTR6), UNK117.4 (RED)
/N$LEDR118: IC8.17 (OUTR2), UNK118.4 (RED)
/N$LEDR119: IC8.37 (OUTR10), UNK119.4 (RED)
/N$LEDR120: IC8.40 (OUTR14), UNK120.4 (RED)
/SCLK: IC1.2 (SCLK), IC2.2 (SCLK), IC3.2 (SCLK), IC4.2 (SCLK), IC5.2 (SCLK), IC6.2 (SCLK), IC7.2 (SCLK), IC8.2 (SCLK), IC10.4 (Y)
/SCLK_FPGA: IC10.2 (A), SV1.7
/SIN_1,2: IC2.1 (SIN), SV1.12
/SIN_3,4: IC4.1 (SIN), SV1.11
/SIN_5,6: IC6.1 (SIN), SV1.10
/SIN_7,8: IC8.1 (SIN), SV1.9
/SOUT2: IC1.1 (SIN)
/SOUT4: IC3.1 (SIN)
/SOUT5: IC5.28 (SOUT)
/SOUT6: IC5.1 (SIN), IC6.28 (SOUT)
/SOUT7: IC7.28 (SOUT)
/SOUT8: IC7.1 (SIN), IC8.28 (SOUT)

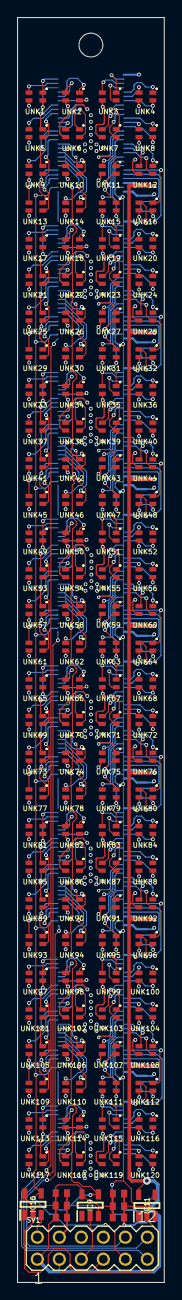
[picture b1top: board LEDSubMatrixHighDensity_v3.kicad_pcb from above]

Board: 4 copper layers, 16.9 x 146.0 mm, 155 parts (0 on the bottom side), 335 nets.

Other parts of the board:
@HOLE0: (no value)
